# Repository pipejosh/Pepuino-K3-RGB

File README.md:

# Pepuino K3 RGB 

Introducing the Pepuino K3 RGB, this is a custom macro pad made from scratch, currently designed to fit any rythm game like osu or geometry dash. The Pepuino K3 has 3 programable switches per light RGB lightning and a rotary encoder.

I made this project because I felt like it was time to jump from keyboard to a more small macro pad. I was orignally gonna buy one, but what a better opportunity to learn how to make one myself.

## Mode

In this current set up I have 2 layers, the Osu mode (ESC, z , x) and the Geometry Dash mode (Space , z , x) you can difference them by the led profile, the purple for Osu and the rainbow for Geometry Dash 

# Technical stuff

### SCHEMATIC DIAGRAM

### PCB 

### CASE RENDER

### BOM
####  Components

| Item            | Description         | Qty | Unit Price | Total Price |
|----------------|--------------------|-----|------------|------------|
| xiao rp2040    | —                  | 1   | 4,54       | 4,54       |
| blank keycaps  | white              | 20  | 0,19       | 3,77       |
| switches       | mechanical switches| 10  | 0,39       | 3,9        |
| rotary encoder | —                  | 1   | 1,85       | 1,85       |
| M2 standoff    | M2 standoff 5mm    | 50  | 0,05       | 2,47       |
| M2 screw       | 5mm screw          | 50  | 0,03       | 1,65       |

#### Taxes

| Item  | Description     | Total Price |
|-------|----------------|------------|
| taxes | aliexpress tax | 4,28       |

#### Components Subtotal

| Category   | Total |
|------------|--------|
| Components | 22,46  |

---

#### PCB

| Item            | Description                | Qty |
|-----------------|---------------------------|-----|
| JLCPCB          | Pepuino Pad PCB           | 1   |
| JLCPCB Shipping | Shipping for PCB + taxes  | 3   |

---

#### Grand Total

| TOTAL |
|-------|
| 26,46 |

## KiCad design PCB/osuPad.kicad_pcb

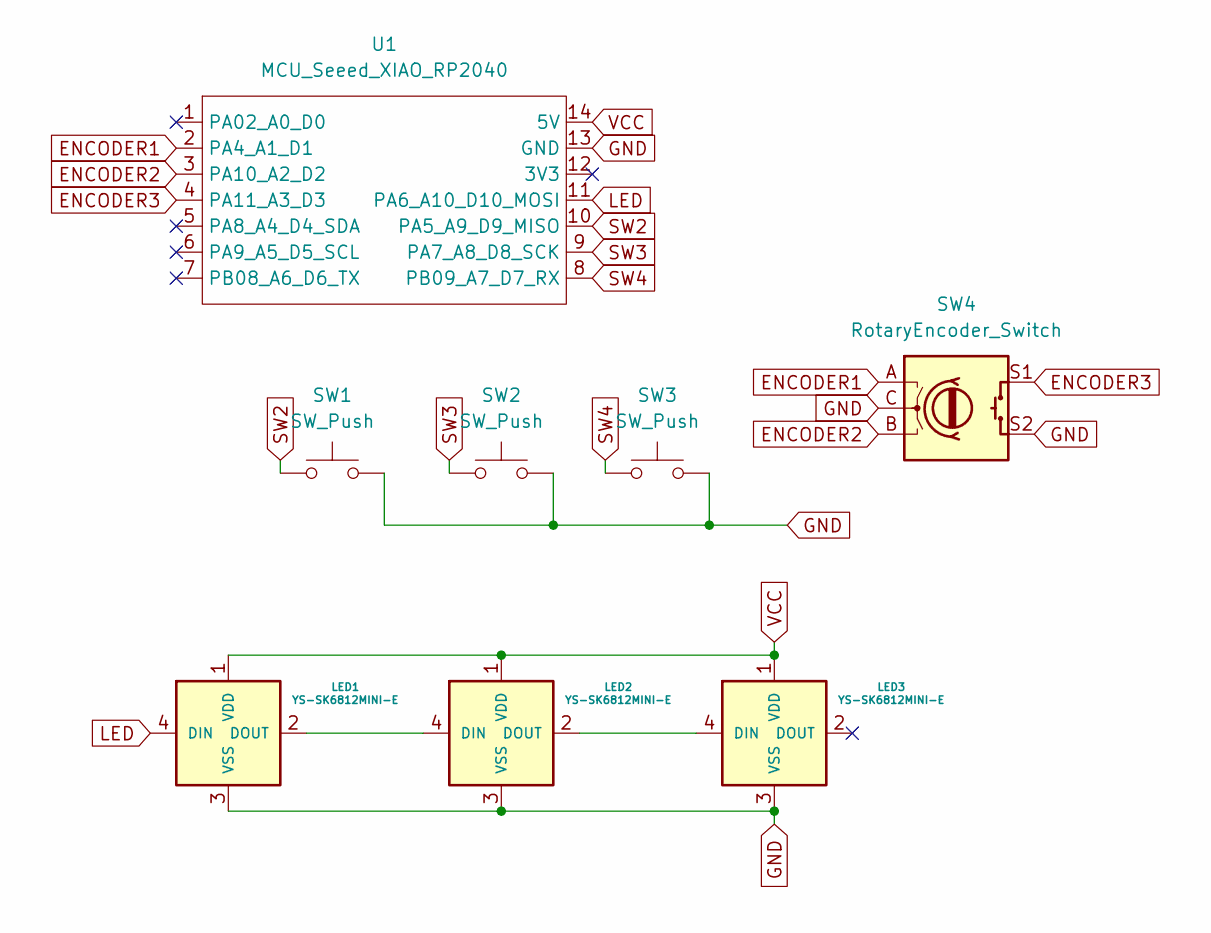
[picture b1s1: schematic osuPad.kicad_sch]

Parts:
LED1, LED2, LED3: YS-SK6812MINI-E
SW1, SW2, SW3: SW_Push; Hotswap_MX_1.00u
SW4: RotaryEncoder_Switch; RotaryEncoder_Alps_EC11E-Switch_Vertical_H20mm
U1: MCU_Seeed_XIAO_RP2040; Seeed_XIAO_RP2040

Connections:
3V3: U1.12 (3V3)
ENCODER1: SW4.A, U1.2 (PA4_A1_D1)
ENCODER2: SW4.B, U1.3 (PA10_A2_D2)
ENCODER3: SW4.S1, U1.4 (PA11_A3_D3)
GND: LED1.3 (VSS), LED2.3 (VSS), LED3.3 (VSS), SW1.2, SW2.2, SW3.2, SW4.C, SW4.S2, U1.13 (GND)
LED: LED1.4 (DIN), U1.11 (PA6_A10_D10_MOSI)
unnamed: LED1.2 (DOUT), LED2.4 (DIN)
unnamed: LED2.2 (DOUT), LED3.4 (DIN)
SCL: U1.6 (PA9_A5_D5_SCL)
SDA: U1.5 (PA8_A4_D4_SDA)
SW2: SW1.1, U1.10 (PA5_A9_D9_MISO)
SW3: SW2.1, U1.9 (PA7_A8_D8_SCK)
SW4: SW3.1, U1.8 (PB09_A7_D7_RX)
VCC: LED1.1 (VDD), LED2.1 (VDD), LED3.1 (VDD), U1.14 (5V)

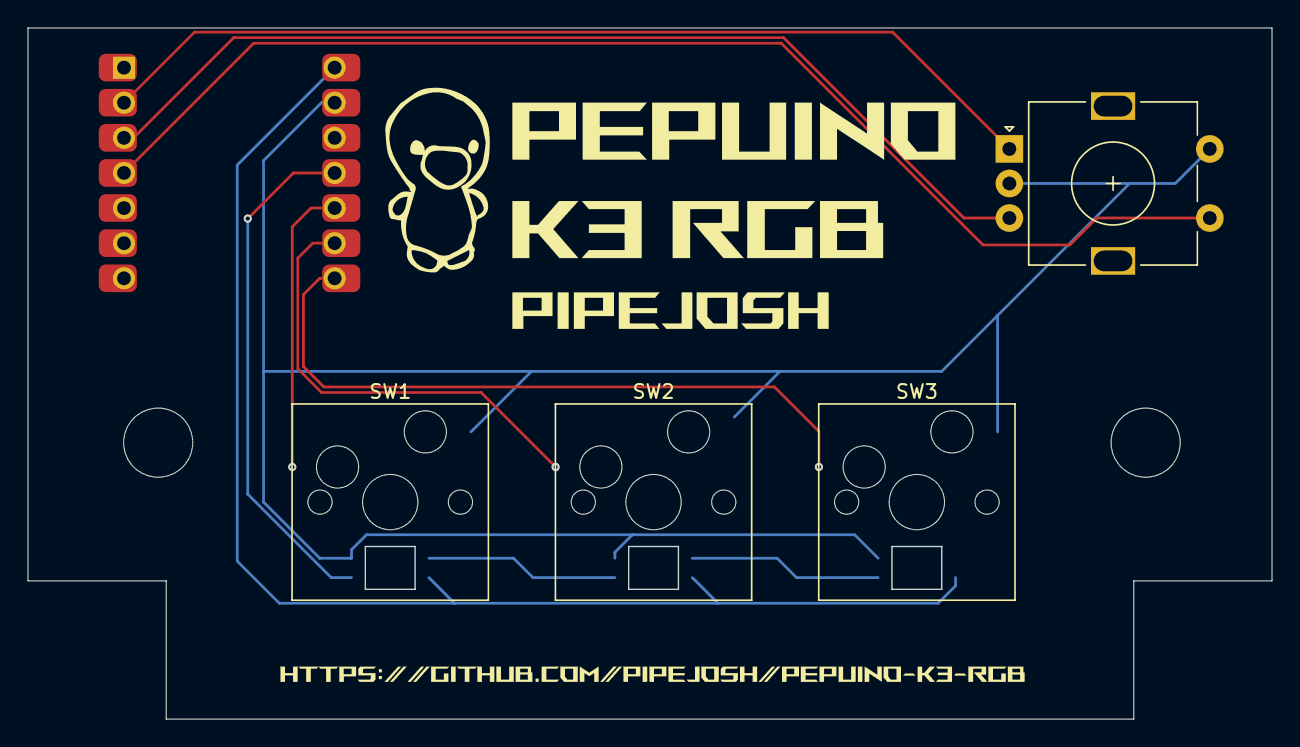
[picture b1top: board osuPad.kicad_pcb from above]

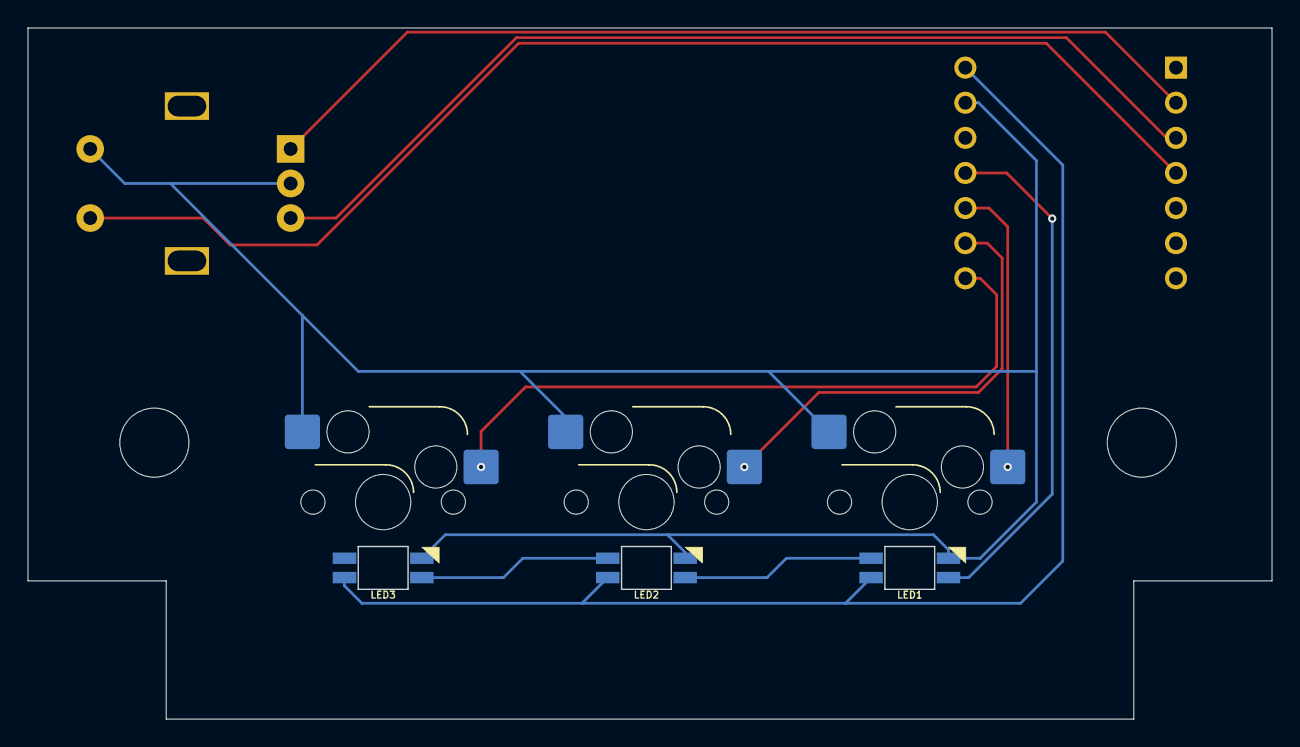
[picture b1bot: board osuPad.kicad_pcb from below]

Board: 2 copper layers, 90.0 x 50.0 mm, 8 parts (3 on the bottom side), 11 nets.

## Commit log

2025-11-30 Created the case
    The case is doneeEeEEeEeeeee!!!
2025-11-30 create document structure
2025-11-30 add README.md
2025-11-30 fix image bug
2025-11-30 add firmware (not tested yet just sketch)
2025-11-30 add schematic
2025-11-30 update BOM
2026-02-19 update pcb, case, and readme
2026-02-19 update img and readme
2026-02-19 update image
2026-02-19 Rename PCB image reference in README
2026-02-19 Rename pcb.png to pcbImage.png
2026-02-19 Fix PCB image filename in README
    Updated PCB image reference in README.md.
2026-02-19 add bom
2026-02-19 Add BOM section with components and pricing details
    Added Bill of Materials (BOM) section with components, taxes, and totals.
2026-02-19 Update PCB image in README
